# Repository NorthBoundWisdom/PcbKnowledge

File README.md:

# PcbKnowledge

PcbKnowledge supplies Git-native engineering knowledge from a design brief to a
manufacturable PCB: validated parts, original footprints, deterministic expansion,
and exported-board checks. It is a knowledge base serving PcbAtlas, which owns
placement, routing, DRC and fabrication output.

See the [current acceptance table](docs/golden-designs.md#current-acceptance) for
the golden designs and [`TODO.md`](TODO.md) for exact stage receipts. Parked
handoffs are not placed or routed boards. Hardware bring-up remains owner-only.

## Use

The [consumer guide](docs/consumer-guide.md) covers pinned bundles, expansion,
handoff files and judged reports for a layout-tool integrator.

Git and Python 3.11+ are required; runtime code uses the standard library.

```bash
python3 configs/pcbknowledge_workflow.py config
python3 configs/pcbknowledge_workflow.py build
python3 configs/pcbknowledge_agent.py --repo . v2 validate
python3 configs/pcbknowledge_agent.py --repo . part search --role monitor.current
python3 configs/pcbknowledge_agent.py --repo . v2 coverage evals/golden-designs/g1.block-graph.json
python3 configs/pcbknowledge_agent.py --repo . v2 coverage --all
python3 configs/pcbknowledge_agent.py --repo . v2 coverage --all --json
python3 configs/pcbknowledge_agent.py --repo . bundle build
python3 configs/pcbknowledge_workflow.py open --workspace .
```

The viewer runs at `http://127.0.0.1:18080/`; keep the terminal open and use Ctrl+C
to stop. Select a citation to inspect its source evidence. The GUI and query CLI are
read-only. Missing facts stay explicit; generation refuses rather than guesses.

`coverage --all` prints one JSON line per brief, retaining every preserved graph,
block readiness, eligibility and typed refusals. Missing graphs are `NOT_RUN` and
incomplete coverage exits 2. Use `--json` for one aggregate report or `--human` for
a readable summary. The single-graph command remains JSON. Coverage is not a fresh synthesis receipt.
The [golden-design corpus](docs/golden-designs.md) defines positive variants and
negative refusal cases, with query-mediated independent evaluation.

## Workspaces and evidence

```bash
python3 configs/pcbknowledge_workspace.py init <workspace> --init-git
python3 configs/pcbknowledge_workspace.py validate <workspace>
```

A workspace is one Git repository with pinned schemas, registries and canonical
JSON records. Select it with `--workspace` or `--repo`; explicit selection never
falls back. Initialization never stages, commits or pushes.

Source originals stay in ignored `.pcbknowledge/evidence/sha256/` caches. Public
Git and packages contain small original metadata and citations. Cache absence is
`NOT_LOCALLY_VERIFIED`. Explicit cache imports are separate from read-only queries:

```bash
python3 configs/pcbknowledge_agent.py --repo . evidence fetch --source source:example
python3 configs/pcbknowledge_agent.py --repo . evidence add /path/to/original.pdf
python3 configs/pcbknowledge_agent.py --repo . v2 audit
```

Use an existing eligible source ID. Fetch/add never edit knowledge or Git; changed
bytes remain separate and failed fetches do not bypass access restrictions.
`v2 validate` rejects unreachable parts, packages and sources. See [local workflow](docs/local-workflow.md),
[architecture](docs/architecture.md), [knowledge model](docs/knowledge-model-v2.md)
and [public-source boundary](docs/open-source-boundary.md).

## Verify

```bash
python3 configs/check_commits.py origin/main..HEAD
python3 configs/check_code_style.py
python3 configs/check_english_repo.py
python3 configs/check_public_repo.py
python3 configs/check_pdfjs_vendor.py
python3 configs/pcbknowledge_workspace.py validate .
python3 configs/pcbknowledge_workflow.py config
python3 configs/pcbknowledge_workflow.py build
python3 configs/pcbknowledge_workflow.py test
python3 configs/pcbknowledge_agent.py --repo . v2 validate
python3 configs/pcbknowledge_workflow.py package
```

Read [`AGENTS.md`](AGENTS.md), [`CONTRIBUTING.md`](CONTRIBUTING.md) and
[`THIRD_PARTY_NOTICES.md`](THIRD_PARTY_NOTICES.md). Report vulnerabilities through
[`SECURITY.md`](SECURITY.md).

Software and repository documentation use [Apache-2.0](LICENSE) unless stated
otherwise. Vendor assets and cited engineering documents retain their own rights.

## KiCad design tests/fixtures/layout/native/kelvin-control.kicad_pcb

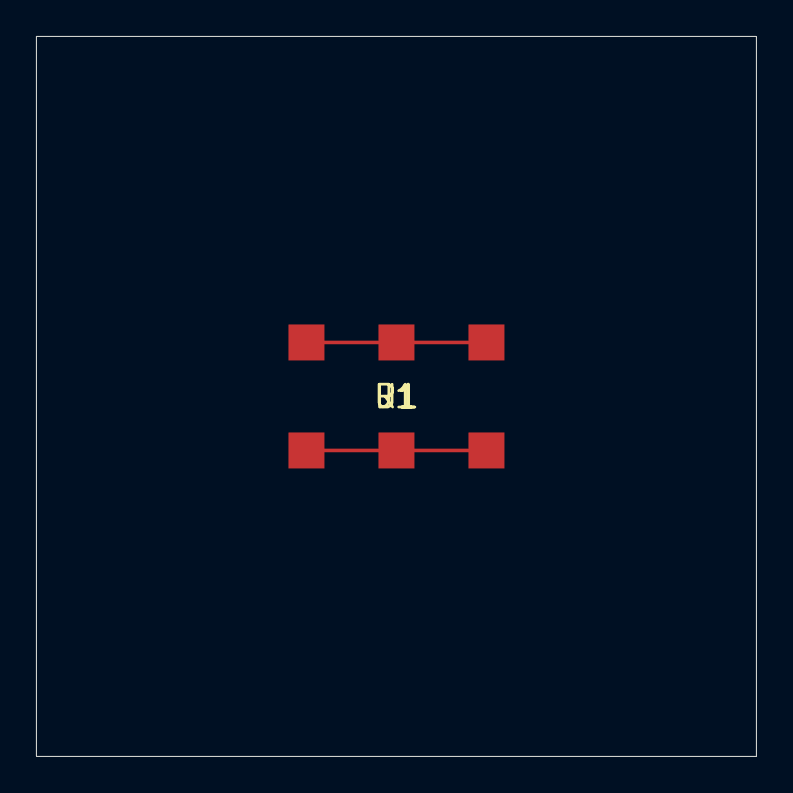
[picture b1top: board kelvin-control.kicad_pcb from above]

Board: 2 copper layers, 40.0 x 40.0 mm, 3 parts (0 on the bottom side), 2 nets.

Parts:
J1: kelvin
R1: kelvin
U1: kelvin

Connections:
N: J1.2, R1.2, U1.2
P: J1.1, R1.1, U1.1
